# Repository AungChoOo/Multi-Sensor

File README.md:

<h1>Multi-Sensor</h1>

<h2>13 in 1 multi-sensor breadboard compatible module.</h2>

- IMU sensor([BMI088](https://www.bosch-sensortec.com/products/motion-sensors/imus/bmi088/))
- Magnetometer([BMM150](https://www.bosch-sensortec.com/products/motion-sensors/magnetometers/bmm150/))
- Gas Sensors([BME680](https://www.bosch-sensortec.com/products/environmental-sensors/gas-sensors/bme680/))

<h2>Rendered Image</h2>

<h2>Front and Back Side</h2>

## License
Resources of this repository are distributed under MIT License. 
See [LICENSE](./LICENSE).

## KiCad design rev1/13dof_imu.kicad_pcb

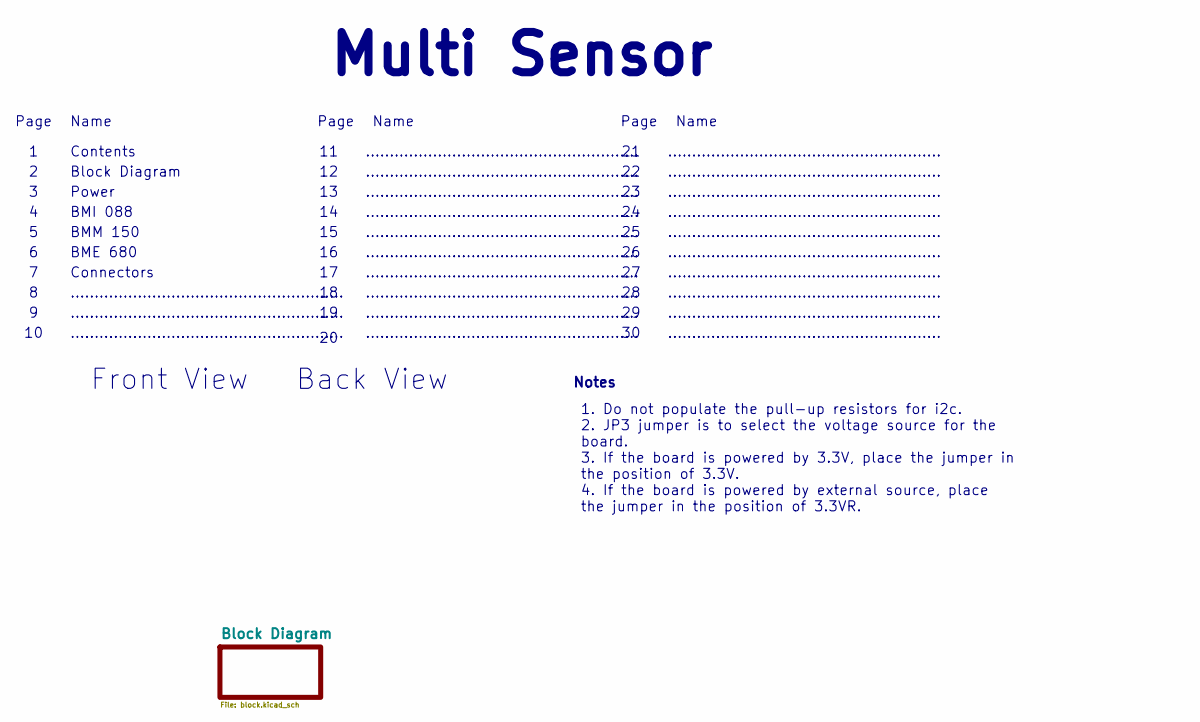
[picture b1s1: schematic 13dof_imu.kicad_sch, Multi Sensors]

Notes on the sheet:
1. Do not populate the pull-up resistors for i2c. 2. JP3 jumper is to select the voltage source for the board. 3. If the board is powered by 3.3V, place the jumper in the position of 3.3V. 4. If the board is powered by external source, place the jumper in the position of 3.3VR.
.........................................................
Front View
Notes
Page
Power
Name
Block Diagram
Multi Sensor
Connectors
BMM 150
BME 680
Back View
BMI 088
Contents

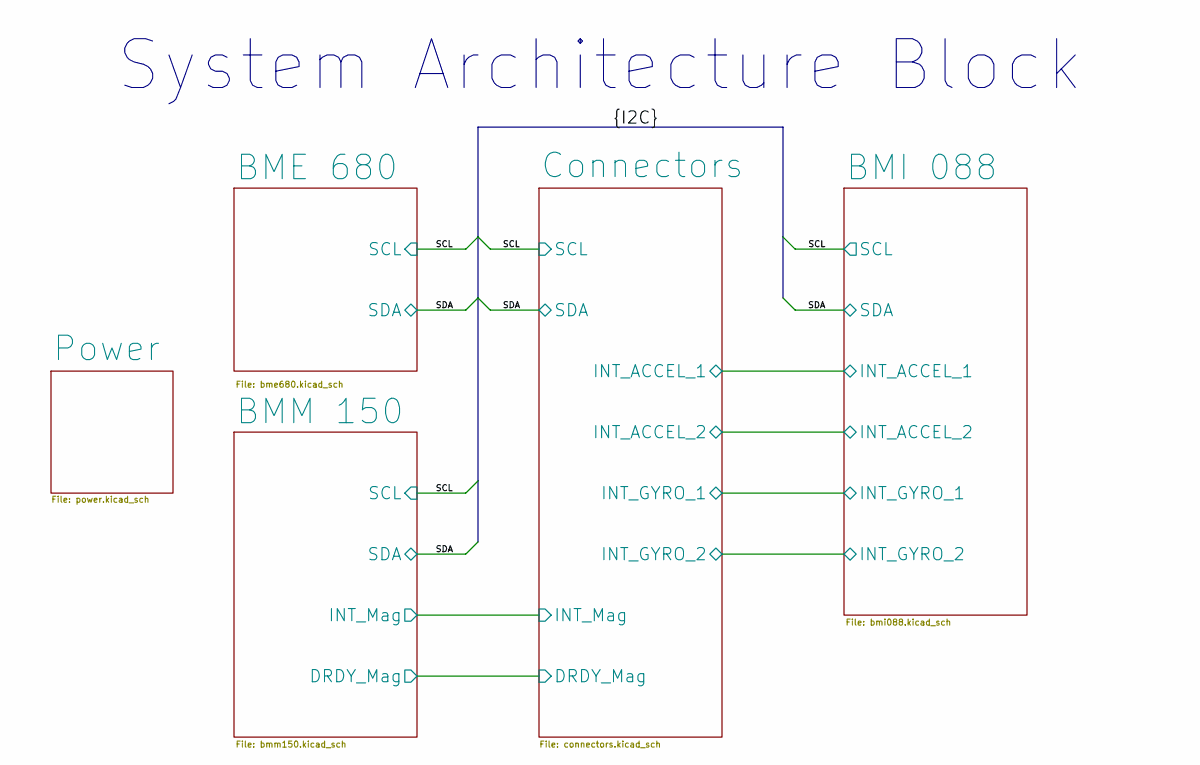
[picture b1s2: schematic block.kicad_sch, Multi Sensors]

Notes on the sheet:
System Architecture Block

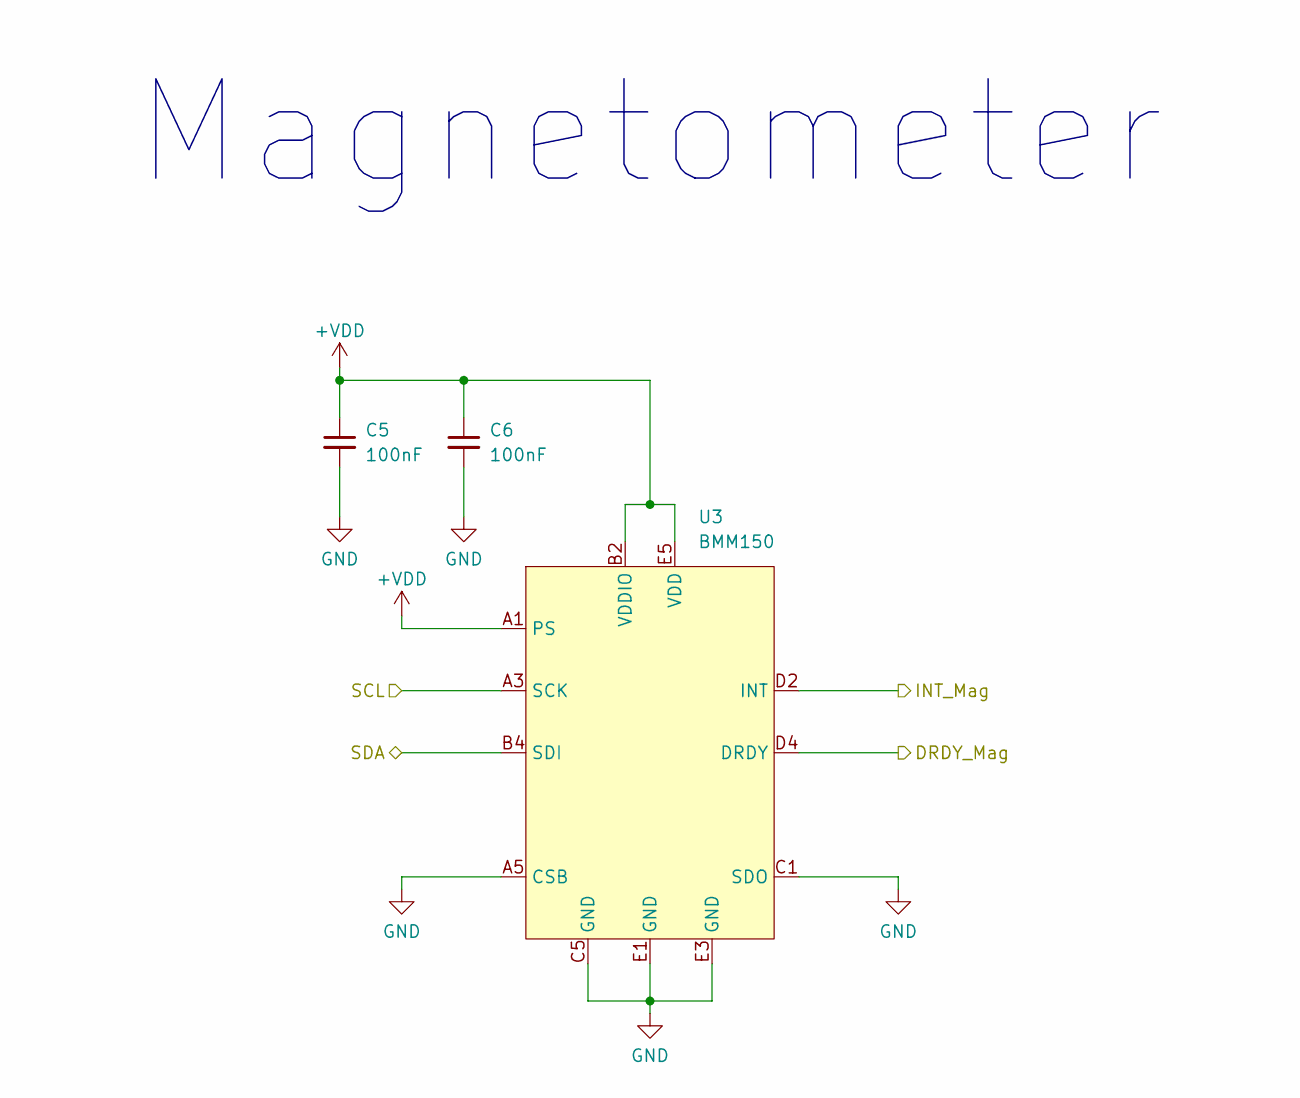
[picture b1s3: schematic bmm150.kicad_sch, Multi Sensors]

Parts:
C5, C6: 100nF; C_0402_1005Metric
U3: BMM150

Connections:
+VDD: C5.1, C6.1, U3.A1 (PS), U3.B2 (VDDIO), U3.E5 (VDD); also elsewhere on the board
/Block Diagram/BMM 150/DRDY_Mag: U3.D4 (DRDY); also elsewhere on the board
/Block Diagram/BMM 150/INT_Mag: U3.D2 (INT); also elsewhere on the board
/Block Diagram/SCL: U3.A3 (SCK); also elsewhere on the board
/Block Diagram/SDA: U3.B4 (SDI); also elsewhere on the board
GND: C5.2, C6.2, U3.A5 (CSB), U3.C1 (SDO), U3.C5 (GND), U3.E1 (GND), U3.E3 (GND); also elsewhere on the board

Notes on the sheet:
Magnetometer

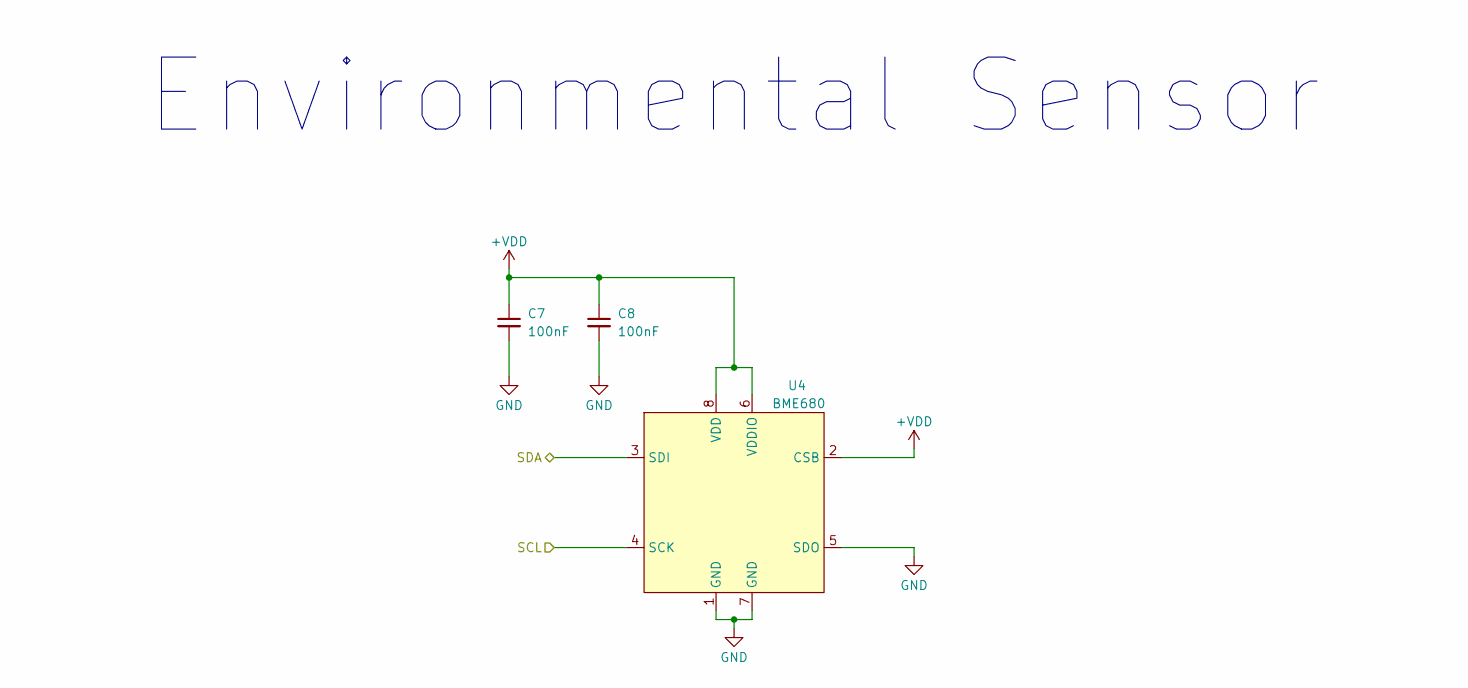
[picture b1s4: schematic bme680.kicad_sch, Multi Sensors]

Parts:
C7, C8: 100nF; C_0402_1005Metric
U4: BME680

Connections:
+VDD: C7.1, C8.1, U4.2 (CSB), U4.6 (VDDIO), U4.8 (VDD); also elsewhere on the board
/Block Diagram/SCL: U4.4 (SCK); also elsewhere on the board
/Block Diagram/SDA: U4.3 (SDI); also elsewhere on the board
GND: C7.2, C8.2, U4.1 (GND), U4.5 (SDO), U4.7 (GND); also elsewhere on the board

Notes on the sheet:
Environmental Sensor

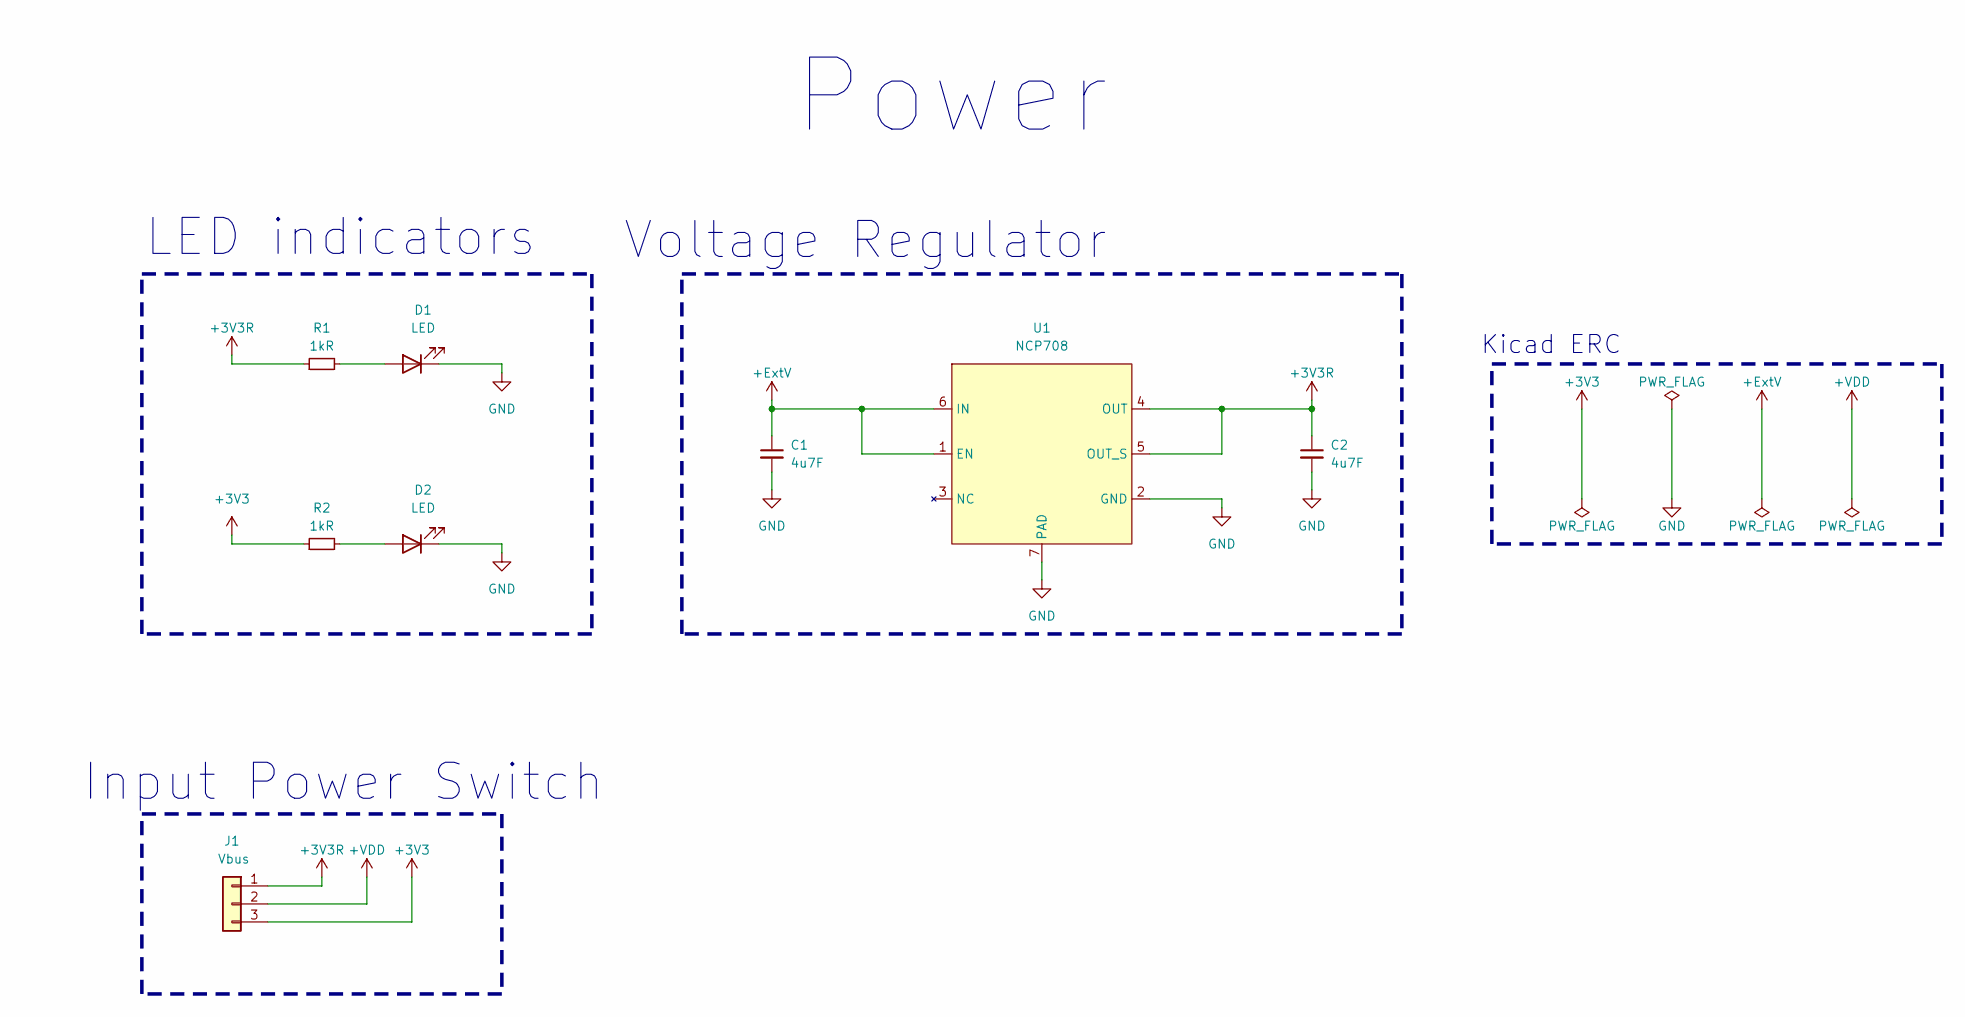
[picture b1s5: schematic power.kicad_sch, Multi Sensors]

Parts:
C1, C2: 4u7F; C_0402_1005Metric
D1, D2: LED; LED_0805_2012
J1: Vbus; PinHeader_1x03_P2.54mm_Vertical
R1, R2: 1kR; R_0402_1005Metric
U1: NCP708

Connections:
+3V3: J1.3, R2.1; also elsewhere on the board
+3V3R: C2.1, J1.1, R1.1, U1.4 (OUT), U1.5 (OUT_S)
+ExtV: C1.1, U1.1 (EN), U1.6 (IN); also elsewhere on the board
+VDD: J1.2; also elsewhere on the board
GND: C1.2, C2.2, D1.1 (K), D2.1 (K), U1.2 (GND), U1.7 (PAD); also elsewhere on the board
unnamed: D1.2 (A), R1.2
unnamed: D2.2 (A), R2.2

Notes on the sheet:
Power
LED indicators
Voltage Regulator
Input Power Switch
Kicad ERC

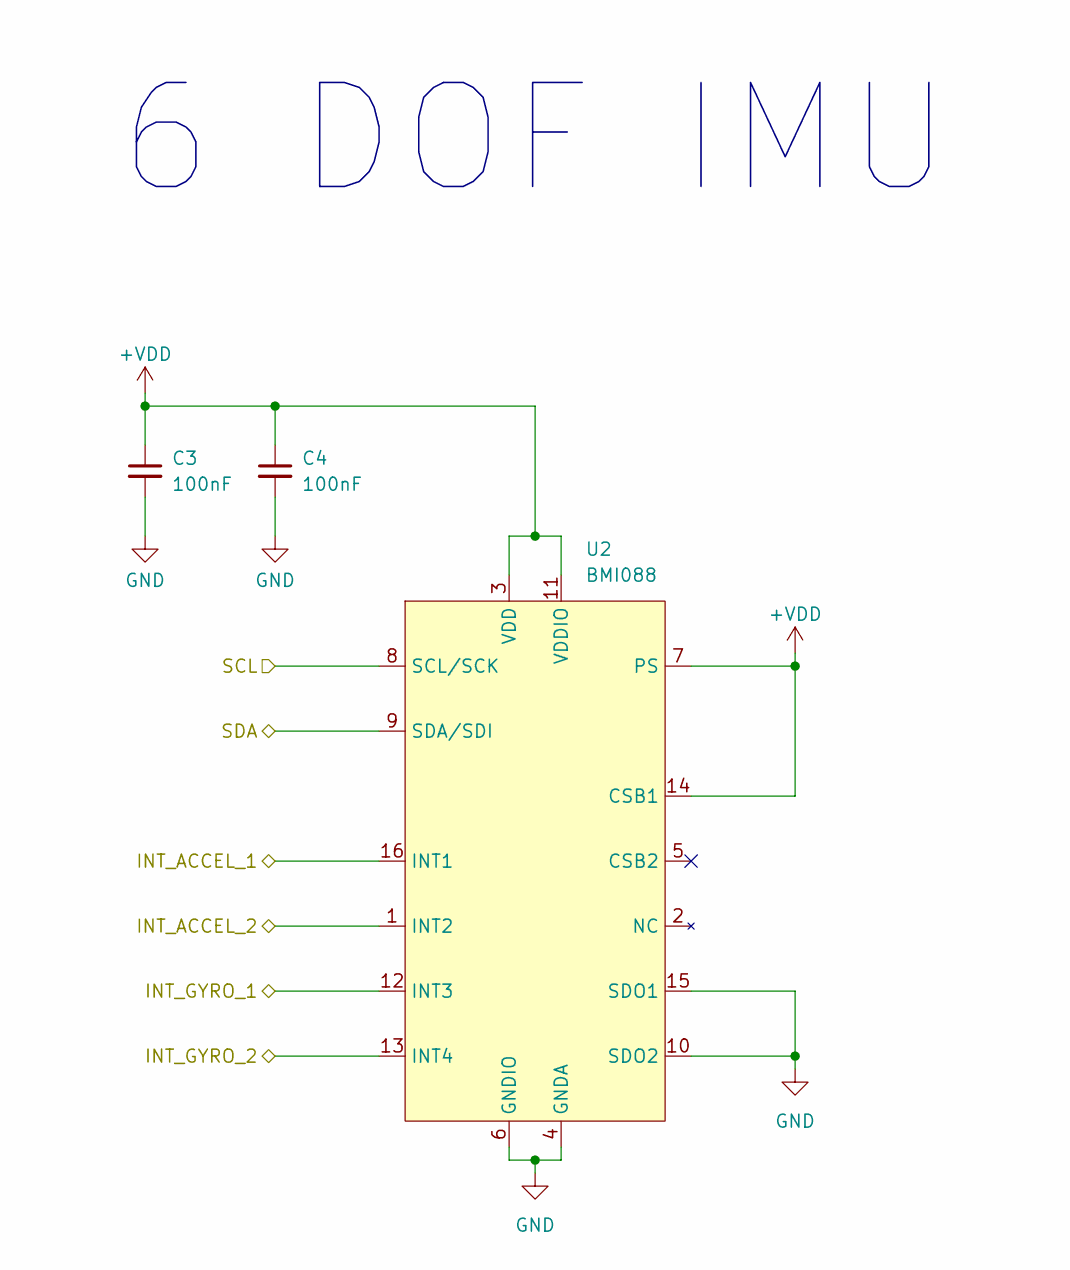
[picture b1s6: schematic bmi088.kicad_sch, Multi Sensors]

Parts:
C3, C4: 100nF; C_0402_1005Metric
U2: BMI088

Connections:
+VDD: C3.1, C4.1, U2.3 (VDD), U2.7 (PS), U2.11 (VDDIO), U2.14 (CSB1); also elsewhere on the board
/Block Diagram/BMI 088/INT_ACCEL_1: U2.16 (INT1); also elsewhere on the board
/Block Diagram/BMI 088/INT_ACCEL_2: U2.1 (INT2); also elsewhere on the board
/Block Diagram/BMI 088/INT_GYRO_1: U2.12 (INT3); also elsewhere on the board
/Block Diagram/BMI 088/INT_GYRO_2: U2.13 (INT4); also elsewhere on the board
/Block Diagram/SCL: U2.8 (SCL/SCK); also elsewhere on the board
/Block Diagram/SDA: U2.9 (SDA/SDI); also elsewhere on the board
GND: C3.2, C4.2, U2.4 (GNDA), U2.6 (GNDIO), U2.10 (SDO2), U2.15 (SDO1); also elsewhere on the board

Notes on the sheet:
6 DOF IMU

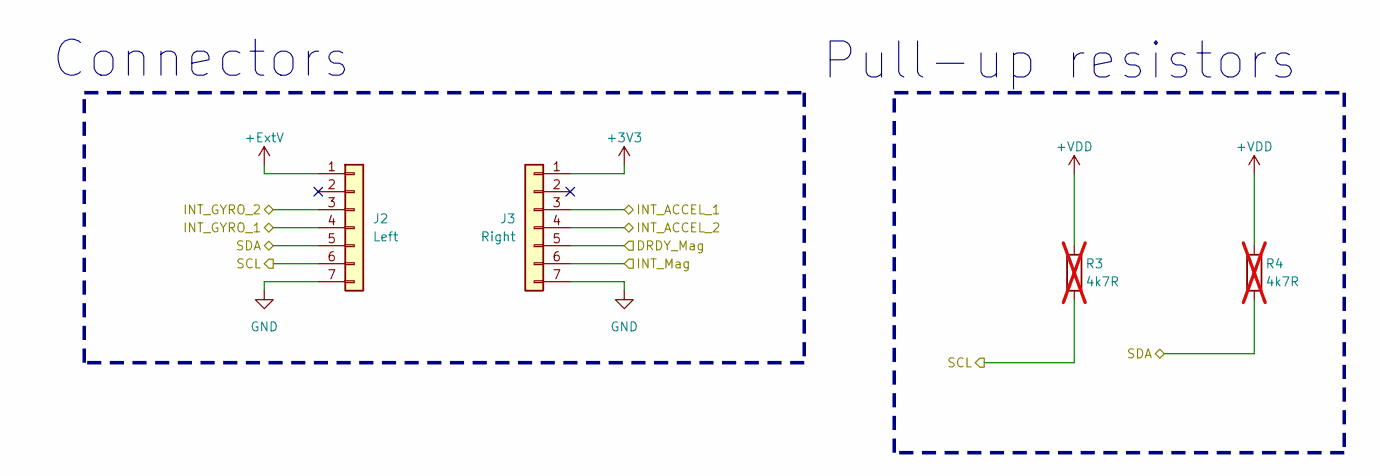
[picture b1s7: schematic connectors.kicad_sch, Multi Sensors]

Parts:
J2: Left; PinHeader_1x07_P2.54mm_Vertical
J3: Right; PinHeader_1x07_P2.54mm_Vertical
R3, R4: 4k7R; R_0402_1005Metric; not fitted

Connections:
+3V3: J3.1; also elsewhere on the board
+ExtV: J2.1; also elsewhere on the board
+VDD: R3.1, R4.1; also elsewhere on the board
/Block Diagram/BMI 088/INT_ACCEL_1: J3.3; also elsewhere on the board
/Block Diagram/BMI 088/INT_ACCEL_2: J3.4; also elsewhere on the board
/Block Diagram/BMI 088/INT_GYRO_1: J2.4; also elsewhere on the board
/Block Diagram/BMI 088/INT_GYRO_2: J2.3; also elsewhere on the board
/Block Diagram/BMM 150/DRDY_Mag: J3.5; also elsewhere on the board
/Block Diagram/BMM 150/INT_Mag: J3.6; also elsewhere on the board
/Block Diagram/SCL: J2.6, R3.2; also elsewhere on the board
/Block Diagram/SDA: J2.5, R4.2; also elsewhere on the board
GND: J2.7, J3.7; also elsewhere on the board

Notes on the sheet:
Connectors
Pull-up resistors

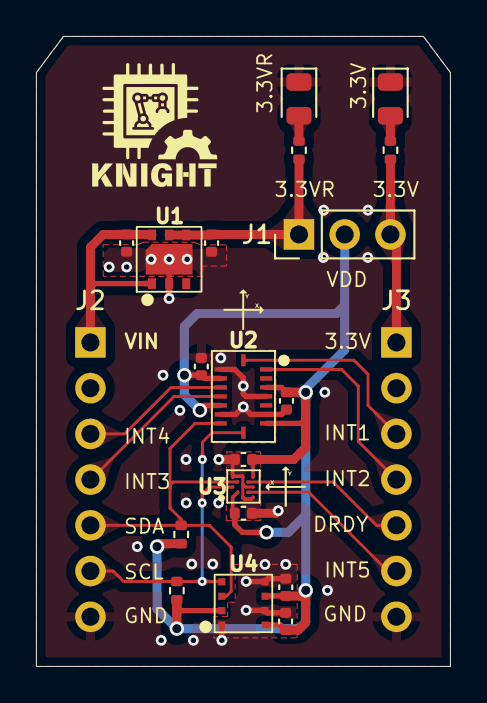
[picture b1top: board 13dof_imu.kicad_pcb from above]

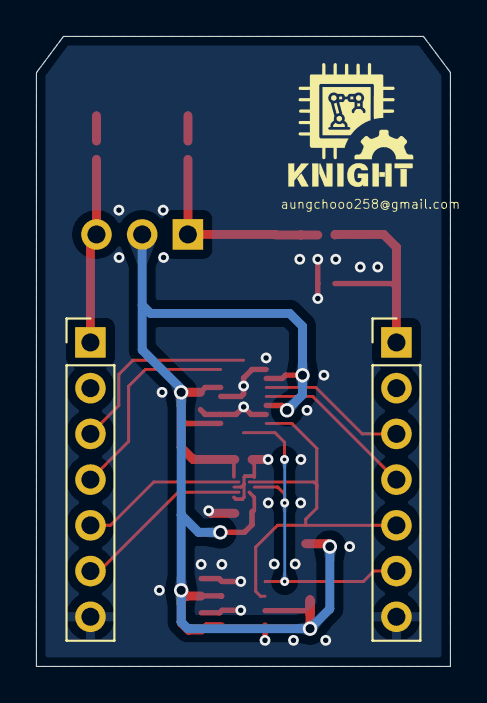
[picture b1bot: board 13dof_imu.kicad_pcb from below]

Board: 4 copper layers, 23.0 x 35.0 mm, 21 parts (2 on the bottom side), 15 nets.

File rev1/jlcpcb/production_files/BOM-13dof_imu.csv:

Comment,Designator,Footprint,LCSC,Quantity
1kR,"R1,R2",R_0402_1005Metric,C11702,2
BME680,U4,BME680,C125972,1
100nF,"C3,C4,C5,C6,C7,C8",C_0402_1005Metric,C1525,6
BMM150,U3,BMM150,C171681,1
NCP708,U1,NCP708,C183178,1
BMI088,U2,BMI088,C194919,1
LED,"D1,D2",LED_0805_2012,C2297,2
4u7F,"C1,C2",C_0402_1005Metric,C23733,2
4k7R,R4,R_0402_1005Metric,C25900,1
Vbus,J1,PinHeader_1x03_P2.54mm_Vertical,C6332196,1
Right,J3,PinHeader_1x07_P2.54mm_Vertical,,1
Left,J2,PinHeader_1x07_P2.54mm_Vertical,,1

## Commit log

2025-01-13 Rev1
2025-01-13 Added README
